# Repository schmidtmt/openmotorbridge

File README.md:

# OpenMotorBridge (v10.0) - Universal Motorcycle Intercom & Telemetry Bridge

<p align="center">
  
  &nbsp;&nbsp;&nbsp;&nbsp;&nbsp;&nbsp;&nbsp;&nbsp;
  
</p>

<p align="center">

</p>

**OpenMotorBridge (OMB)** is an open-source, cross-vendor communication and telemetry bridge for motorcycles. It seamlessly interconnects proprietary wireless intercom systems (**Sena Mesh 3.0** and **Cardo DMC Gen2**) with an open **2.4 GHz / 868 MHz OpenMotorMesh (OMM)**, high-precision **GNSS Tour Logging (Automotive Dead Reckoning)**, and a **wireless WebBLE PWA cockpit dashboard**.

---

## 📚 Technical Documentation

The comprehensive technical specification is split into 18 logically organized chapters:

1. [**01 - System Architecture & Satellite Topology**](docs/en/01_system_architecture.md)  
   *The 5 standardized functional nodes, de-sensing philosophy, RF diversity, whitepaper engineering decisions, and cockpit integration.*

2. [**02 - Intercom Matrix, Hardware Profiles & Routing**](docs/en/02_intercom_matrix_profiles.md)  
   *The 5 OEM adapter classes A-E, LittleFS profile engine, zero-latency PTT (< 1.8 ms), and audio cross-matrix.*

3. [**03 - Audio DSP, Acoustics & Knowles MEMS Wind Tracking**](docs/en/03_audio_dsp_acoustics.md)  
   *1500V Bourns isolation, ES8388 Codec, Knowles MEMS acoustic wind sampling, and Raised-Cosine Ducking.*

4. [**04 - Mesh Network, LoRa & GNSS Navigation**](docs/en/04_mesh_lora_navigation.md)  
   *OpenMotorMesh (OMM), Dynamic Leader Election (DLE), 868 MHz LoRa fallback, and 10 Hz Multi-GNSS.*

5. [**05 - Power Management, UPS Battery & Power Gate**](docs/en/05_power_management_ups.md)  
   *LM5164-Q1 72V buck, BQ24075 UPS, TPS25921 Quad-eFuse, Front Node TPS54302 / SW3526 30W PD & 1-click CarPlay hard reboot.*

6. [**06 - Telemetry Blackbox, SDIO Ringbuffer & WebDAV Sync**](docs/en/06_telemetry_blackbox_webdav.md)  
   *4-bit high-speed SDIO, GDPR/court-compliant ringbuffer, ECDSA SHA-256, and automated private cloud sync.*

7. [**07 - Hardware Architecture & Board Pinouts (All 10 PCBAs)**](docs/en/07_pcba_hardware_pinouts.md)  
   *All 10 active circuit boards: layer stackup, controlled impedance, net classes, functional zoning, and pinout tables (`PCBA 01`, `03`, `05`, `05B`, `05C`, `05D`, `07`, `08`, `09`, `10`).*

8. [**08 - Mechanical Enclosures, CAD & Reference Mounting Kits**](docs/en/08_enclosures_mechanics_cad.md)  
   *Screwless Dual-Rail Slide-In Monocoques (Type A & B), Under-Perch Mirror Pod (`PCBA 05C`), 5-Port Glovebox Hub (`PCBA 05B`), Sensor Puck (`PCBA 05D`), Radar 2.0 Winged Housing with Garmin Bayonet, and 4-pin IP67 magnetic breakaway couplers.*

9. [**09 - Firmware Architecture, FreeRTOS & Rollback-OTA**](docs/en/09_firmware_architecture.md)  
   *Multi-core ESP32-S31 (Main) & ESP32-P4 + ESP32-E22 (Front), Pod Co-Processors (ESP32-C6), ESP-NOW low-latency protocol (< 1.8 ms), and dual-bank rollback OTA.*

10. [**10 - WebApp PWA & Dashboard Operation**](docs/en/10_webapp_pwa_dashboard.md)  
    *Zero-cloud PWA web app, Web Bluetooth API (WebBLE), vehicle dynamics HUD, Front Node controls, Support-Van / Convoy profile modes, and 4-tier GPX export.*

11. [**11 - Smart-Managed CarPlay & Android Auto Bridge Architecture (PCBA 05)**](docs/en/11_carplay_android_auto_bridge_architecture.md)  
    *Harley Skyline OS / Boom! Box integration, CP2AA protocol bridge, Virtual WHIM bypass, source-gated handlebar controls & headless dongle management.*

12. [**12 - Vehicle CAN-Bus Profiles, DBC JSON Schema & Universal Telemetry Engine**](docs/en/12_can_bus_vehicle_profiles.md)  
    *Data-driven LittleFS profiles for Harley-Davidson, BMW Motorrad, KTM, and OBD2, passive listen-only protection, and EKF tunnel dead reckoning.*

13. [**13 - Digital Simulation & Multi-Physics Master Testbench**](docs/en/13_simulation_testbench.md)  
    *9 modular Python testbenches and 10 HIL scenarios verifying SPICE, thermal, transients, RF, and acoustics.*

14. [**14 - EMC Hardening, RF Shielding & Environmental Protection**](docs/en/14_emv_rf_hardening.md)  
    *Automotive transient immunity (ISO 7637-2), 2.4 GHz vs 868 MHz isolation, IPC-CC-830B coating, and shock damping.*

15. [**15 - Bill of Materials (BOM) & SMT Manufacturing (All 10 PCBAs)**](docs/en/15_bom_manufacturing.md)  
    *Complete 10-board BOM for JLCPCB SMT production, ordering checklist, two-cable backbone harness, and COTS items.*

16. [**16 - Build Instructions, Wiring & Vehicle Installation**](docs/en/16_build_instructions_assembly.md)  
    *Step-by-step assembly guide for screwless v10 Slide-In Monocoques, 3D printing parameters (FDM vs. MJF), Front Node & Glovebox Hub mounting, Harley 4-pin magnetic side-wall pass-through, Smart-Keyfob build, and commissioning.*

17. [**17 - Automotive Standards & Technical References**](docs/en/17_standards_references.md)  
    *Index for ISO 7637-2, ISO 16750, ECE R10, RED 2014/53/EU, IEC 61672-1 Class 1, and Bluetooth SIG.*

18. [**18 - Legal Compliance, Privacy (GDPR) & Licensing**](docs/en/18_legal_compliance_dsgvo.md)  
    *Open-source licenses (GPL-3.0, CERN-OHL-S v2, CC BY-SA 4.0), GDPR compliance, and liability disclaimer.*

---

## 🛠️ Repository Layout

* **`docs/de/`**: Complete technical specifications in German.
* **`docs/en/`**: Complete technical specifications in English.
* **`firmware/main_controller/`**: ESP-IDF / C++ source code for the central main box (ESP32-S31, PCBA 01).
* **`firmware/front_node/`**: ESP-IDF / C++ source code for the Universal Front Node (ESP32-P4 + ESP32-E22, PCBA 05).
* **`firmware/smart_cartridge/`**: ESP-IDF / C++ source code for Saddlebag Pod Gateways Pod 1 & 2 (ESP32-C6, PCBA 03).
* **`firmware/radar_submcu/`**: ESP-IDF / C++ source code for Heck-Radar 2.0 Sub-MCU & Halo Wings (ESP32-C5, PCBA 08).
* **`webapp_pwa/`**: Zero-cloud offline WebBLE dashboard (HTML5, Vanilla JS, CSS3, Service Worker, i18n).
* **`hardware/`**: KiCad schematics, Gerber files, and 3D enclosure CAD models.
* **`tools/audio_testbench/`**: **Interactive Live Audio DSP Studio & Real-Time Testbench** (`python3 tools/audio_testbench/server.py` $\rightarrow$ Web Audio testbench with live mic, Spacebar PTT, speedometer & ducking).
* **`tools/simulators/`**: 9 modular Python simulation testbenches (`python3 tools/run_all_simulations.py`).

---

## 📜 Licenses

* **Hardware & PCB Layouts:** [CERN-OHL-S v2](https://ohwr.org/project/cernohl/wikis/Documents/CERN-OHL-version-2) (Strongly Reciprocal)
* **Firmware & Web Dashboard:** [GNU General Public License v3.0 (GPL-3.0)](https://www.gnu.org/licenses/gpl-3.0.html)
* **Documentation & 3D Models:** [Creative Commons Attribution-ShareAlike 4.0 International (CC BY-SA 4.0)](https://creativecommons.org/licenses/by-sa/4.0/)

---

## ⚠️ Liability Disclaimer

All information, schematics, board layouts, 3D printing files, and software published in this project are provided free of charge on an "AS IS" basis. Assembly, installation, and operation occur entirely at the user's own risk. All mentioned brand names (Harley-Davidson®, BMW®, Garmin®, Sena®, Cardo®, Apple CarPlay®) are registered trademarks of their respective owners.

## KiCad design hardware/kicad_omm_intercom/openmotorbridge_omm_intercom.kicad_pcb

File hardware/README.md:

# OpenMotorBridge v8.5 / v9.0 - KiCad Hardware-Baukasten (Clean All-UWB Architecture)

Dieses Verzeichnis enthält die vollständigen **KiCad 10 Schaltplan-, PCB- und Produktionsdateien** für die drahtlose **All-UWB & Pure-DC Architektur** von OpenMotorBridge.

---

## 📂 Das bereinigte 6-Platinen-Lineup

Durch den konsequenten Einsatz von Ultra-Wideband (Qorvo DW3110 6.5 GHz Ch. 5, $< 0{,}4\,\text{ms}$) und Bluetooth entfällt jegliche Signal- und NF-Audioverdrahtung über den Rahmen. Der Kabelbaum besteht ausschließlich aus robusten **2-Draht-DC-Power-Peitschen** (+5V/GND bzw. +12V/GND). 

Die Pod-Platine (`PCBA 02`) und der Heck-Pod (`PCBA 04`) sind ersatzlos entfallen - der Baukasten besteht aus **exakt 6 aktiven PCBAs**:

| PCBA | Baugruppe & Funktion | Maße / Lagen | Kern-Komponenten / RF |
| :--- | :--- | :--- | :--- |
| **PCBA 01** | **Zentralbox Main Controller**<br>*(Unter Sitzbank, Audio-DSP, USV)* | 85 x 55 mm<br>4 Lagen (ENIG) | ESP32-S3, ES8388 24-Bit Codec, TCAN334G CAN-FD, LM5164-Q1, SX1262 LoRa (Top), DW3110 UWB (Bottom), SW1 Taster |
| **PCBA 03** | **Universal Smart Cartridge Rev 3.0**<br>*(Autarker UWB-Funkschlitten)* | 35 x 25 mm<br>2 Lagen (ENIG, 2-seitig SMT) | Qorvo DW3110 UWB, SPI Host-MCU, 4x AO3400A MOSFETs, 2P Frontkontakt (+5V/GND), DNP-Codec |
| **PCBA 05** | **Universal Front-Knoten**<br>*(Cockpit Hub, Sensorik, Audio, USB-PD)* | 82 x 50 mm<br>4 Lagen (ENIG) | ESP32-S3, DW3110 UWB, SAM-M10Q, USB2514B Hub, Dual SW3526 PD20W, Qi 12V, BSD LEDs |
| **PCBA 06** | **MagSafe Frame Dock Adapter**<br>*(Rahmendock M8 auf 2-Pin MagSafe)* | 28 x 11.5 mm<br>2 Lagen (1 oz) | 2 Pogo-Pins (+5V / GND), TVS Diode, 16V PPTC Polyfuse |
| **PCBA 07** | **2-in-1 LoRa Smart-Keyfob & Pager**<br>*(Taschen-Pager, N52 Key & Qi)* | 38 x 19 mm<br>2 Lagen (ENIG) | Nordic nRF52840 SoC, Semtech SX1262 LoRa, DRV2605L Haptik, BQ51003 Qi RX |
| **PCBA 08** | **Radar 2.0 Sub-MCU & Wings**<br>*(Wheeltec 77GHz MR20 + Halo LED)* | 115 x 65 mm<br>2 Lagen (ENIG) | ESP32 Sub-MCU (UWB DW3110), 36x WS2812B LEDs, 2-Pin 12V Power |

---

## 🔌 Zentraler Bordnetz-Stecker (Deutsch DTM-12 Automotive)

Die Zentralbox nutzt einen robusten, wasserdichten **Deutsch DTM-12 Industriestecker** (11 aktive Kontakte):

| Pin | Signalname | Funktion | Querschnitt / Ziel |
| :---: | :--- | :--- | :--- |
| **1** | `KL30_IN` | 12V Dauerplus | AWG20 (0.50 mm²) / Bordnetz |
| **2** | `KL15_IGN` | 12V Zündungsplus | AWG22 (0.34 mm²) / Zündung |
| **3** | `VEHICLE_GND`| Hauptmasse (KL31) | AWG20 (0.50 mm²) / Rahmen |
| **4** | `CAN_H` | Fahrzeug-CAN High | AWG24 (0.22 mm²) / Twisted Pair |
| **5** | `CAN_L` | Fahrzeug-CAN Low | AWG24 (0.22 mm²) / Twisted Pair |
| **6** | `POD1_VCC` | 5V Switched Power Bucht 1 (Links) | AWG22 (0.34 mm²) / JWPF 2P |
| **7** | `POD1_GND` | Masse Bucht 1 (Links) | AWG22 (0.34 mm²) / JWPF 2P |
| **8** | `POD2_VCC` | 5V Switched Power Bucht 2 (Rechts) | AWG22 (0.34 mm²) / JWPF 2P |
| **9** | `POD2_GND` | Masse Bucht 2 (Rechts) | AWG22 (0.34 mm²) / JWPF 2P |
| **10**| `RADAR_PWR` | 12V Switched Power Radar Heck | AWG22 (0.34 mm²) / JWPF 2P |
| **11**| `RADAR_GND` | Masse Radar | AWG22 (0.34 mm²) / JWPF 2P |
| **12**| `CHASSIS_EARTH` | Gehäuseschirm / Rahmenerde | AWG20 (0.50 mm²) |

---

## 🛠️ Fertigung & Validierung (JLCPCB / Eurocircuits)

* **Produktionspakete generieren:**
  ```bash
  python3 hardware/scripts/export_manufacturing_packages.py
  ```
* **JLCPCB DFM & Netlist-Verifikation:**
  ```bash
  /Applications/KiCad/KiCad.app/Contents/Frameworks/Python.framework/Versions/3.9/bin/python3 hardware/scripts/verify_pcb_designs_jlcpcb.py
  ```

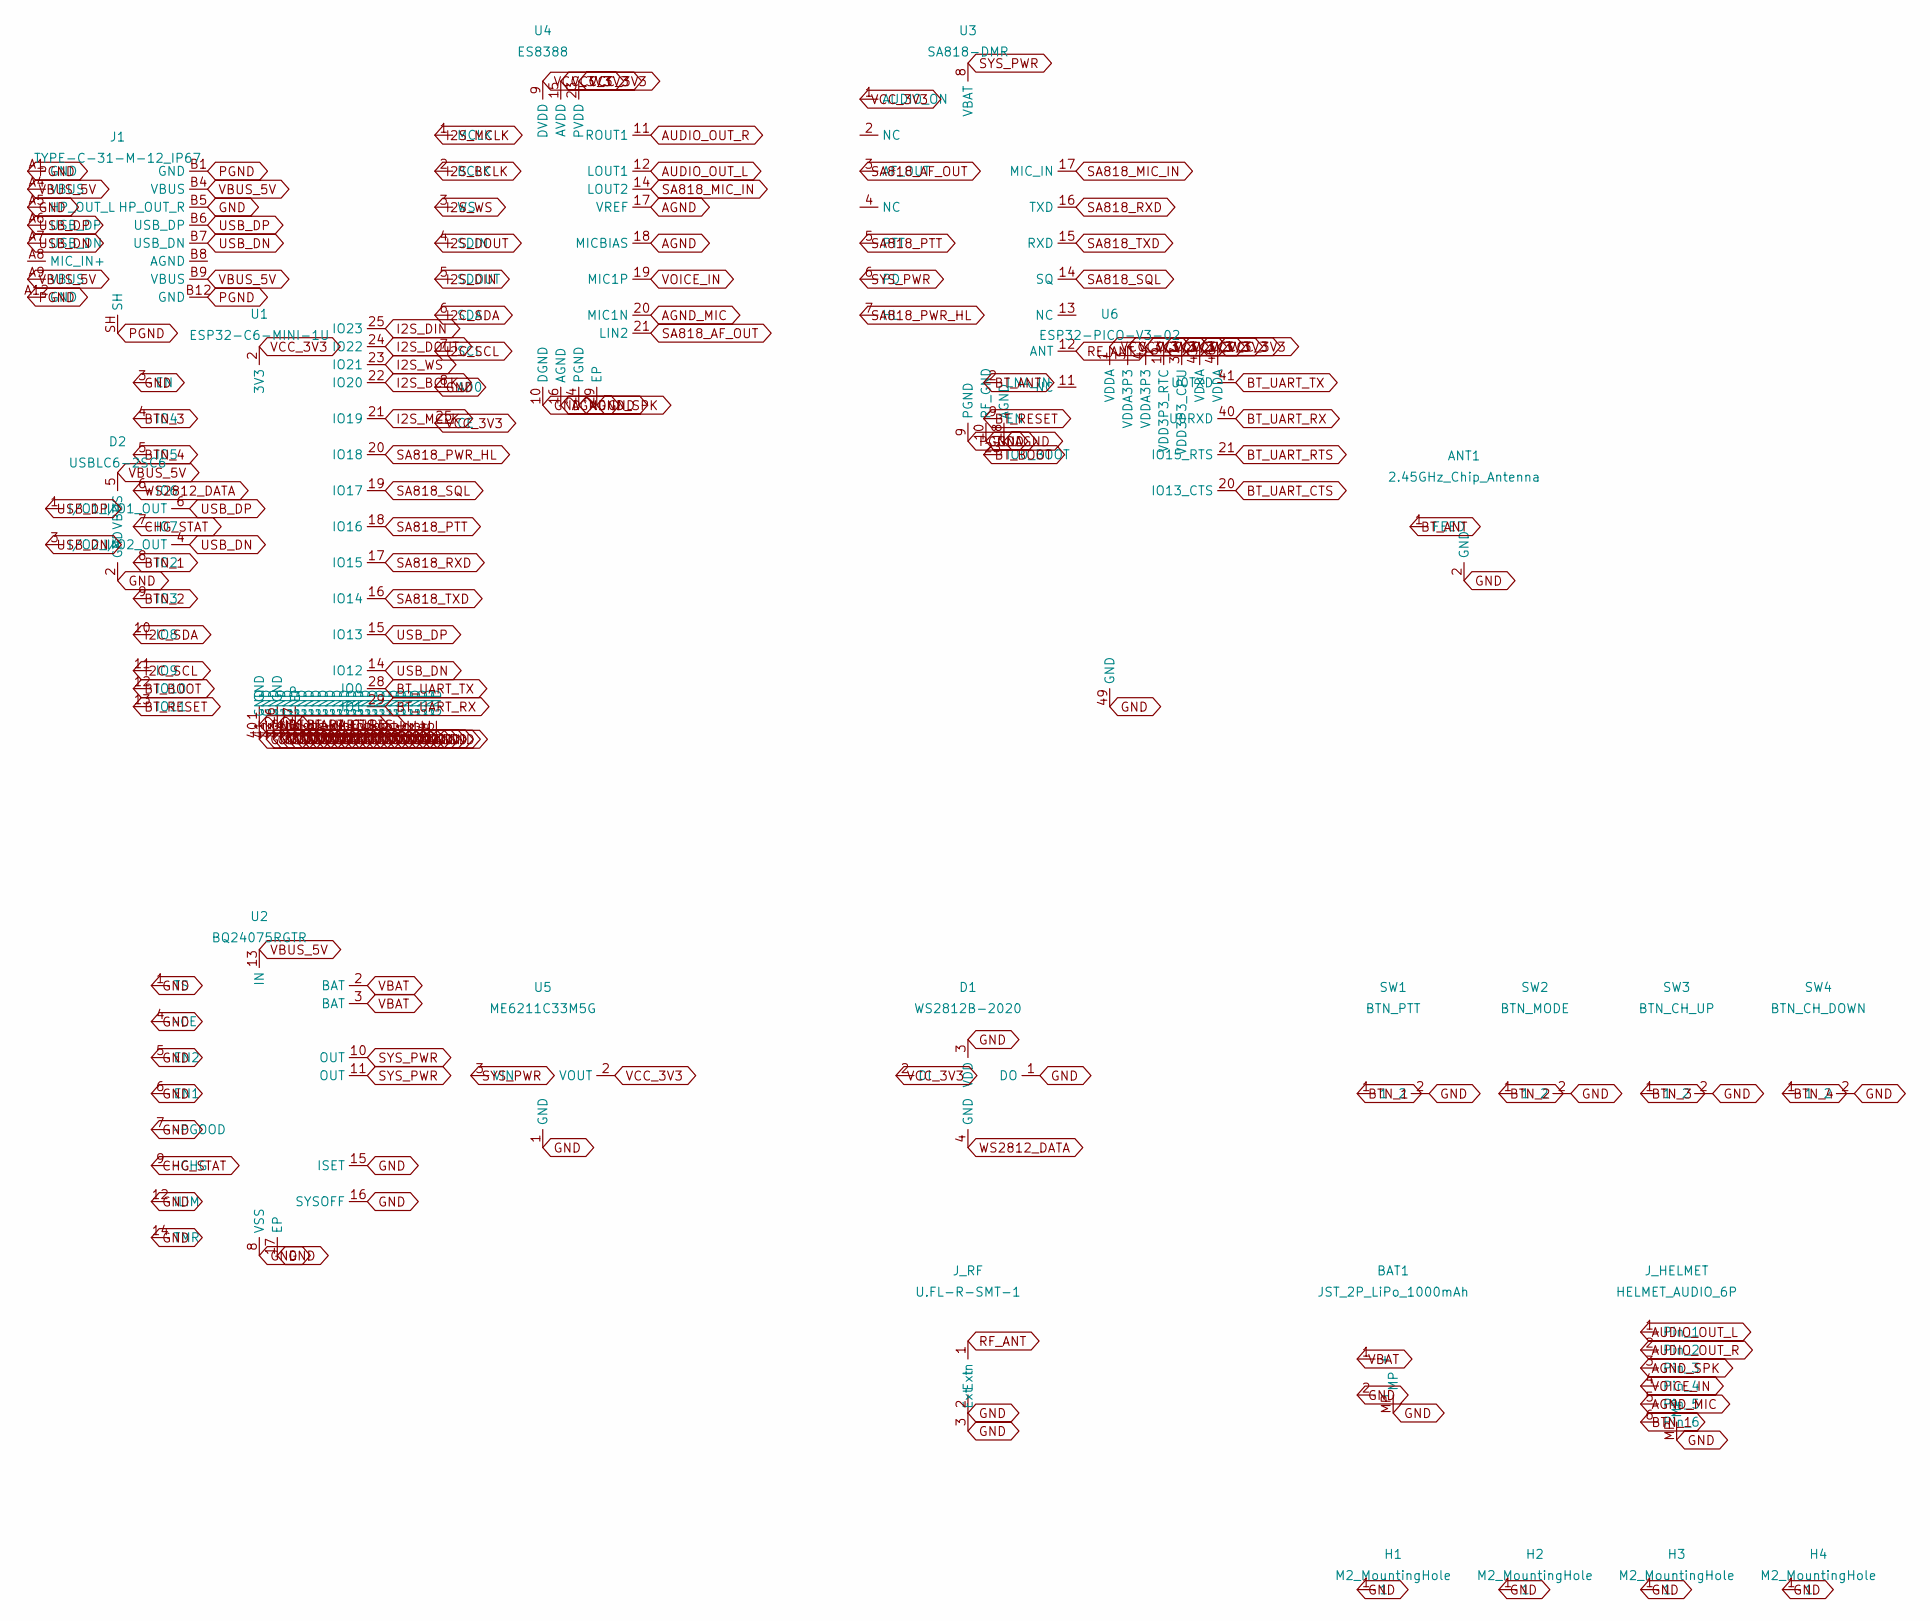
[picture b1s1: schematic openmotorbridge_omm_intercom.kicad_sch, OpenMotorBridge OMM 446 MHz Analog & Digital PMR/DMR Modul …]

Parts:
ANT1: 2.45GHz_Chip_Antenna; Johanson_2450AT18x100; LCSC C2909988
BAT1: JST_2P_LiPo_1000mAh; JST_SH_BM02B-SRSS-TB_1x02-1MP_P1.00mm_Vertical
D1: WS2812B-2020; LED_WS2812B-2020_PLCC4_2.0x2.0mm
D2: USBLC6-2SC6; SOT-23-6
H1, H2, H3, H4: M2_MountingHole; MountingHole_2.2mm_M2_Pad
J1: TYPE-C-31-M-12_IP67; USB_C_Receptacle_HRO_TYPE-C-31-M-12
J_HELMET: HELMET_AUDIO_6P; JST_SH_BM06B-SRSS-TB_1x06-1MP_P1.00mm_Vertical
J_RF: U.FL-R-SMT-1; U.FL_Hirose_U.FL-R-SMT-1_Vertical
SW1: BTN_PTT; SW_Push_SPST_NO_Alps_SKRK
SW2: BTN_MODE; SW_Push_SPST_NO_Alps_SKRK
SW3: BTN_CH_UP; SW_Push_SPST_NO_Alps_SKRK
SW4: BTN_CH_DOWN; SW_Push_SPST_NO_Alps_SKRK
U1: ESP32-C6-MINI-1U; ESP32-S2-MINI-1U
U2: BQ24075RGTR; VQFN-16-1EP_3x3mm_P0.5mm_EP1.8x1.8mm
U3: SA818-DMR; NiceRF_SA818-DMR_SMD_38x16mm
U4: ES8388; QFN-28-1EP_4x4mm_P0.4mm_EP2.4x2.4mm
U5: ME6211C33M5G; SOT-23
U6: ESP32-PICO-V3-02; QFN-48-1EP_7x7mm_P0.5mm_EP5.3x5.3mm; LCSC C2686884

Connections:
AGND: U3.18 (AGND), U4.16 (AGND), U4.17 (VREF), U4.18 (MICBIAS)
AGND_MIC: J_HELMET.5, U4.20 (MIC1N)
AGND_SPK: J_HELMET.3, U4.24 (PGND)
AUDIO_OUT_L: J_HELMET.1, U4.12 (LOUT1)
AUDIO_OUT_R: J_HELMET.2, U4.11 (ROUT1)
BTN_1: J_HELMET.6, SW1.1, U1.8 (IO2)
BTN_2: SW2.1, U1.9 (IO3)
BTN_3: SW3.1, U1.4 (IO4)
BTN_4: SW4.1, U1.5 (IO5)
BT_ANT: ANT1.1 (FEED), U6.2 (LNA_IN)
BT_BOOT: U1.12 (IO10), U6.23 (IO0_BOOT)
BT_RESET: U1.13 (IO11), U6.9 (EN)
BT_UART_CTS: U1.26 (GND), U6.20 (IO13_CTS)
BT_UART_RTS: U1.27 (EP), U6.21 (IO15_RTS)
BT_UART_RX: U1.29 (IO1), U6.40 (U0RXD)
BT_UART_TX: U1.28 (IO0), U6.41 (U0TXD)
CHG_STAT: U1.7 (IO7), U2.9 (~CHG)
GND: ANT1.2 (GND), BAT1.2 (-), BAT1.MP, D1.1 (DO), D1.3 (VDD), D2.2 (GND), H1.1, H2.1, H3.1, H4.1, J1.A5 (HP_OUT_L), J1.B5 (HP_OUT_R), J_HELMET.MP, J_RF.2 (Ext), J_RF.3 (Ext), SW1.2, SW2.2, SW3.2, SW4.2, U1.1 (GND), U1.3 (EN), U1.40 (GND), U1.41 (GND), U1.42 (GND), U1.43 (GND), U1.44 (GND), U1.45 (GND), U1.46 (GND), U1.47 (GND), U1.48 (GND), U1.49 (GND), U1.50 (GND), U1.51 (GND), U1.52 (GND), U1.53 (GND), U1.54 (GND), U1.55 (GND), U1.56 (GND), U1.57 (GND), U1.58 (GND), U1.59 (GND), U1.60 (GND), U1.61 (GND), U1.62 (GND), U1.63 (GND), U1.64 (GND), U1.65 (GND), U2.1 (TS), U2.4 (~CE), U2.5 (EN2), U2.6 (EN1), U2.7 (~PGOOD), U2.8 (VSS), U2.12 (ILIM), U2.14 (TMR), U2.15 (ISET), U2.16 (SYSOFF), U2.17 (EP), U3.10 (RF_GND), U4.8 (AD0), U4.10 (DGND), U4.29 (EP), U5.1 (GND), U6.49 (GND)
I2C_SCL: U1.11 (IO9), U4.7 (SCL)
I2C_SDA: U1.10 (IO8), U4.6 (SDA)
I2S_BCLK: U1.22 (IO20), U4.2 (BCLK)
I2S_DIN: U1.25 (IO23), U4.5 (SDOUT)
I2S_DOUT: U1.24 (IO22), U4.4 (SDIN)
I2S_MCLK: U1.21 (IO19), U4.1 (MCLK)
I2S_WS: U1.23 (IO21), U4.3 (WS)
PGND: J1.A1 (GND), J1.A12 (GND), J1.B1 (GND), J1.B12 (GND), J1.SH, U3.9 (PGND)
RF_ANT: J_RF.1 (In), U3.12 (ANT)
SA818_AF_OUT: U3.3 (AF_OUT), U4.21 (LIN2)
SA818_MIC_IN: U3.17 (MIC_IN), U4.14 (LOUT2)
SA818_PTT: U1.18 (IO16), U3.5 (PTT)
SA818_PWR_HL: U1.20 (IO18), U3.7 (HL)
SA818_RXD: U1.17 (IO15), U3.16 (TXD)
SA818_SQL: U1.19 (IO17), U3.14 (SQ)
SA818_TXD: U1.16 (IO14), U3.15 (RXD)
SYS_PWR: U2.10 (OUT), U2.11 (OUT), U3.6 (PD), U3.8 (VBAT), U5.3 (VIN)
USB_DN: D2.3 (I/O2_IN), D2.4 (I/O2_OUT), J1.A7 (USB_DN), J1.B7 (USB_DN), U1.14 (IO12)
USB_DP: D2.1 (I/O1_IN), D2.6 (I/O1_OUT), J1.A6 (USB_DP), J1.B6 (USB_DP), U1.15 (IO13)
VBAT: BAT1.1 (+), U2.2 (BAT), U2.3 (BAT)
VBUS_5V: D2.5 (VBUS), J1.A4 (VBUS), J1.A9 (VBUS), J1.B4 (VBUS), J1.B9 (VBUS), U2.13 (IN)
VCC_3V3: D1.2 (DI), U1.2 (3V3), U3.1 (AUDIO_ON), U4.9 (DVDD), U4.15 (AVDD), U4.23 (PVDD), U4.25 (CE), U5.2 (VOUT), U6.1 (VDDA), U6.3 (VDDA3P3), U6.4 (VDDA3P3), U6.19 (VDD3P3_RTC), U6.37 (VDD3P3_CPU), U6.43 (VDDA), U6.46 (VDDA)
VOICE_IN: J_HELMET.4, U4.19 (MIC1P)
WS2812_DATA: D1.4 (GND), U1.6 (IO6)

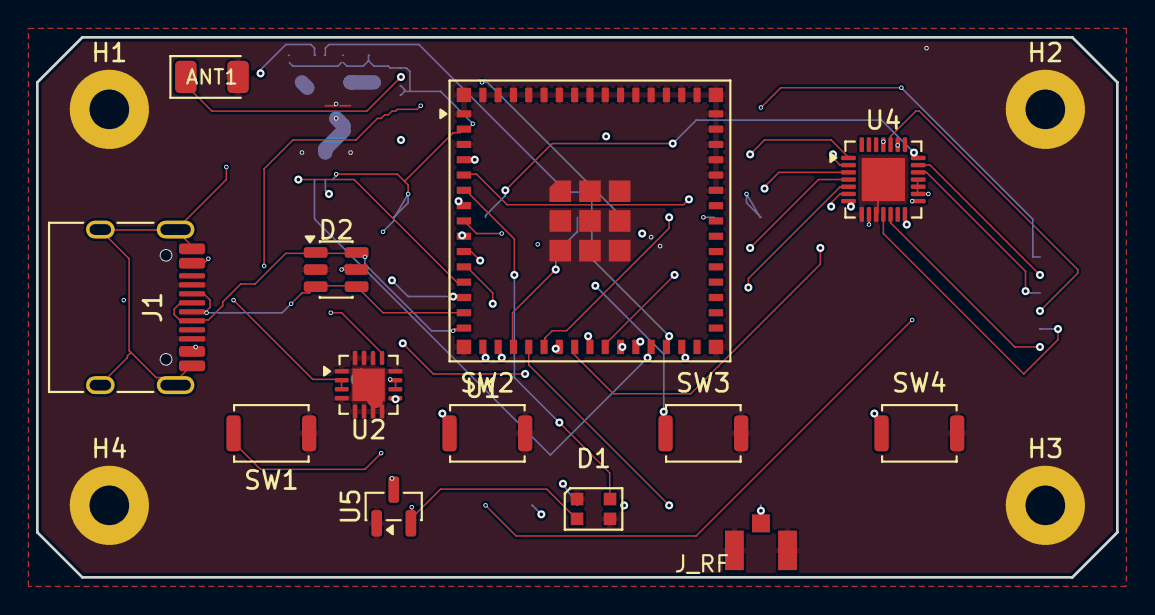
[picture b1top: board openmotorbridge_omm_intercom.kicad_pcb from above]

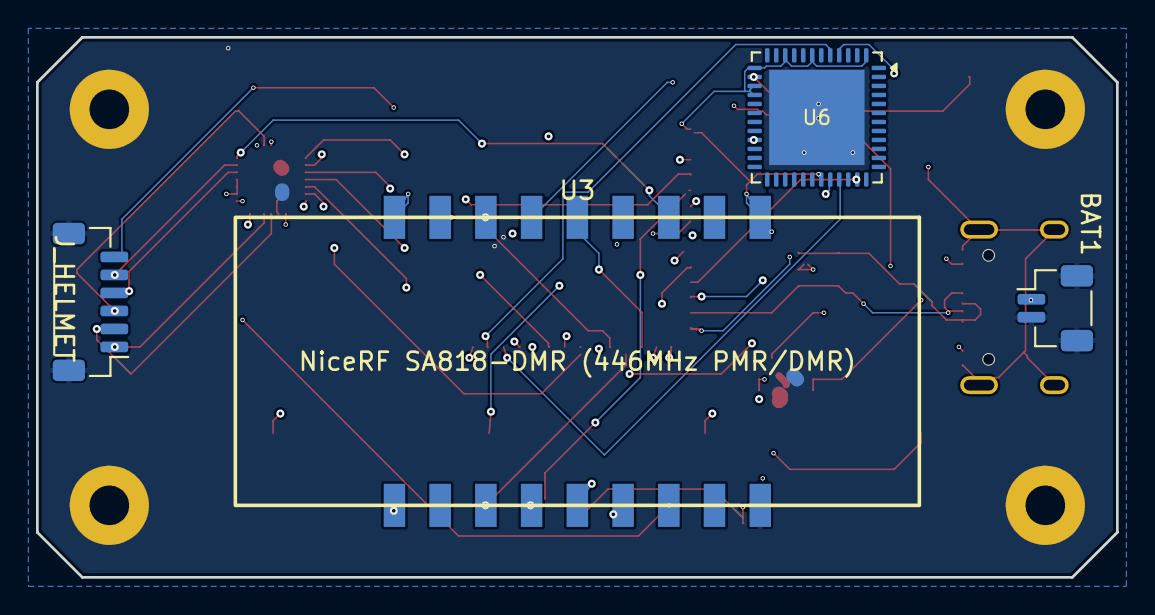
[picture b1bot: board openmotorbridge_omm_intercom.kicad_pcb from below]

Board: 4 copper layers, 60.0 x 30.0 mm, 21 parts (4 on the bottom side), 42 nets.

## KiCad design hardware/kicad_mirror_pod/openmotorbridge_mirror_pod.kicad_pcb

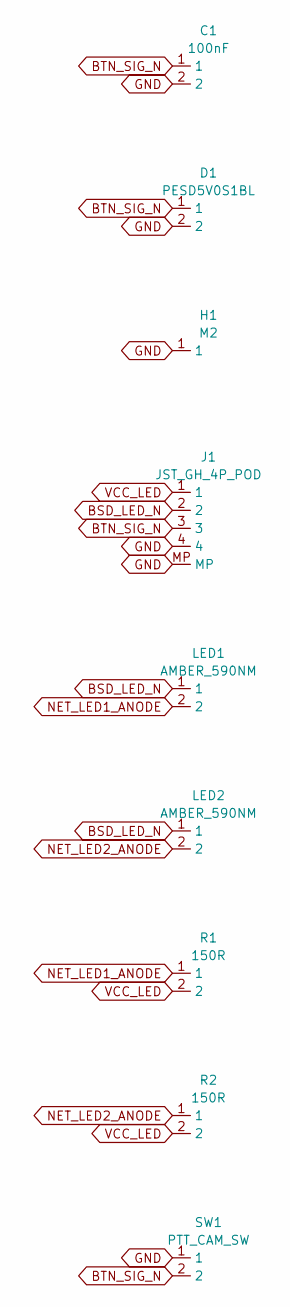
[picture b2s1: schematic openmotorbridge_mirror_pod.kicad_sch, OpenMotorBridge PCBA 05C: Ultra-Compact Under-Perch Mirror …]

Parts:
C1: 100nF; C_0603_1608Metric
D1: PESD5V0S1BL; D_SOD-323
H1: M2; MountingHole_2.2mm_M2_Pad
J1: JST_GH_4P_POD; JST_GH_SM04B-GHS-TB_1x04-1MP_P1.25mm_Horizontal
LED1, LED2: AMBER_590NM; LED_1206_3216Metric
R1, R2: 150R; R_0603_1608Metric
SW1: PTT_CAM_SW; SW_SPST_B3SL-1002P

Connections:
BSD_LED_N: J1.2, LED1.1, LED2.1
BTN_SIG_N: C1.1, D1.1, J1.3, SW1.2
GND: C1.2, D1.2, H1.1, J1.4, J1.MP, SW1.1
NET_LED1_ANODE: LED1.2, R1.1
NET_LED2_ANODE: LED2.2, R2.1
VCC_LED: J1.1, R1.2, R2.2

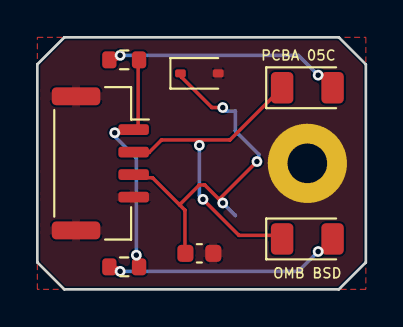
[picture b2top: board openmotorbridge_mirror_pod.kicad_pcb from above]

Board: 2 copper layers, 18.2 x 14.0 mm, 9 parts (1 on the bottom side), 6 nets.

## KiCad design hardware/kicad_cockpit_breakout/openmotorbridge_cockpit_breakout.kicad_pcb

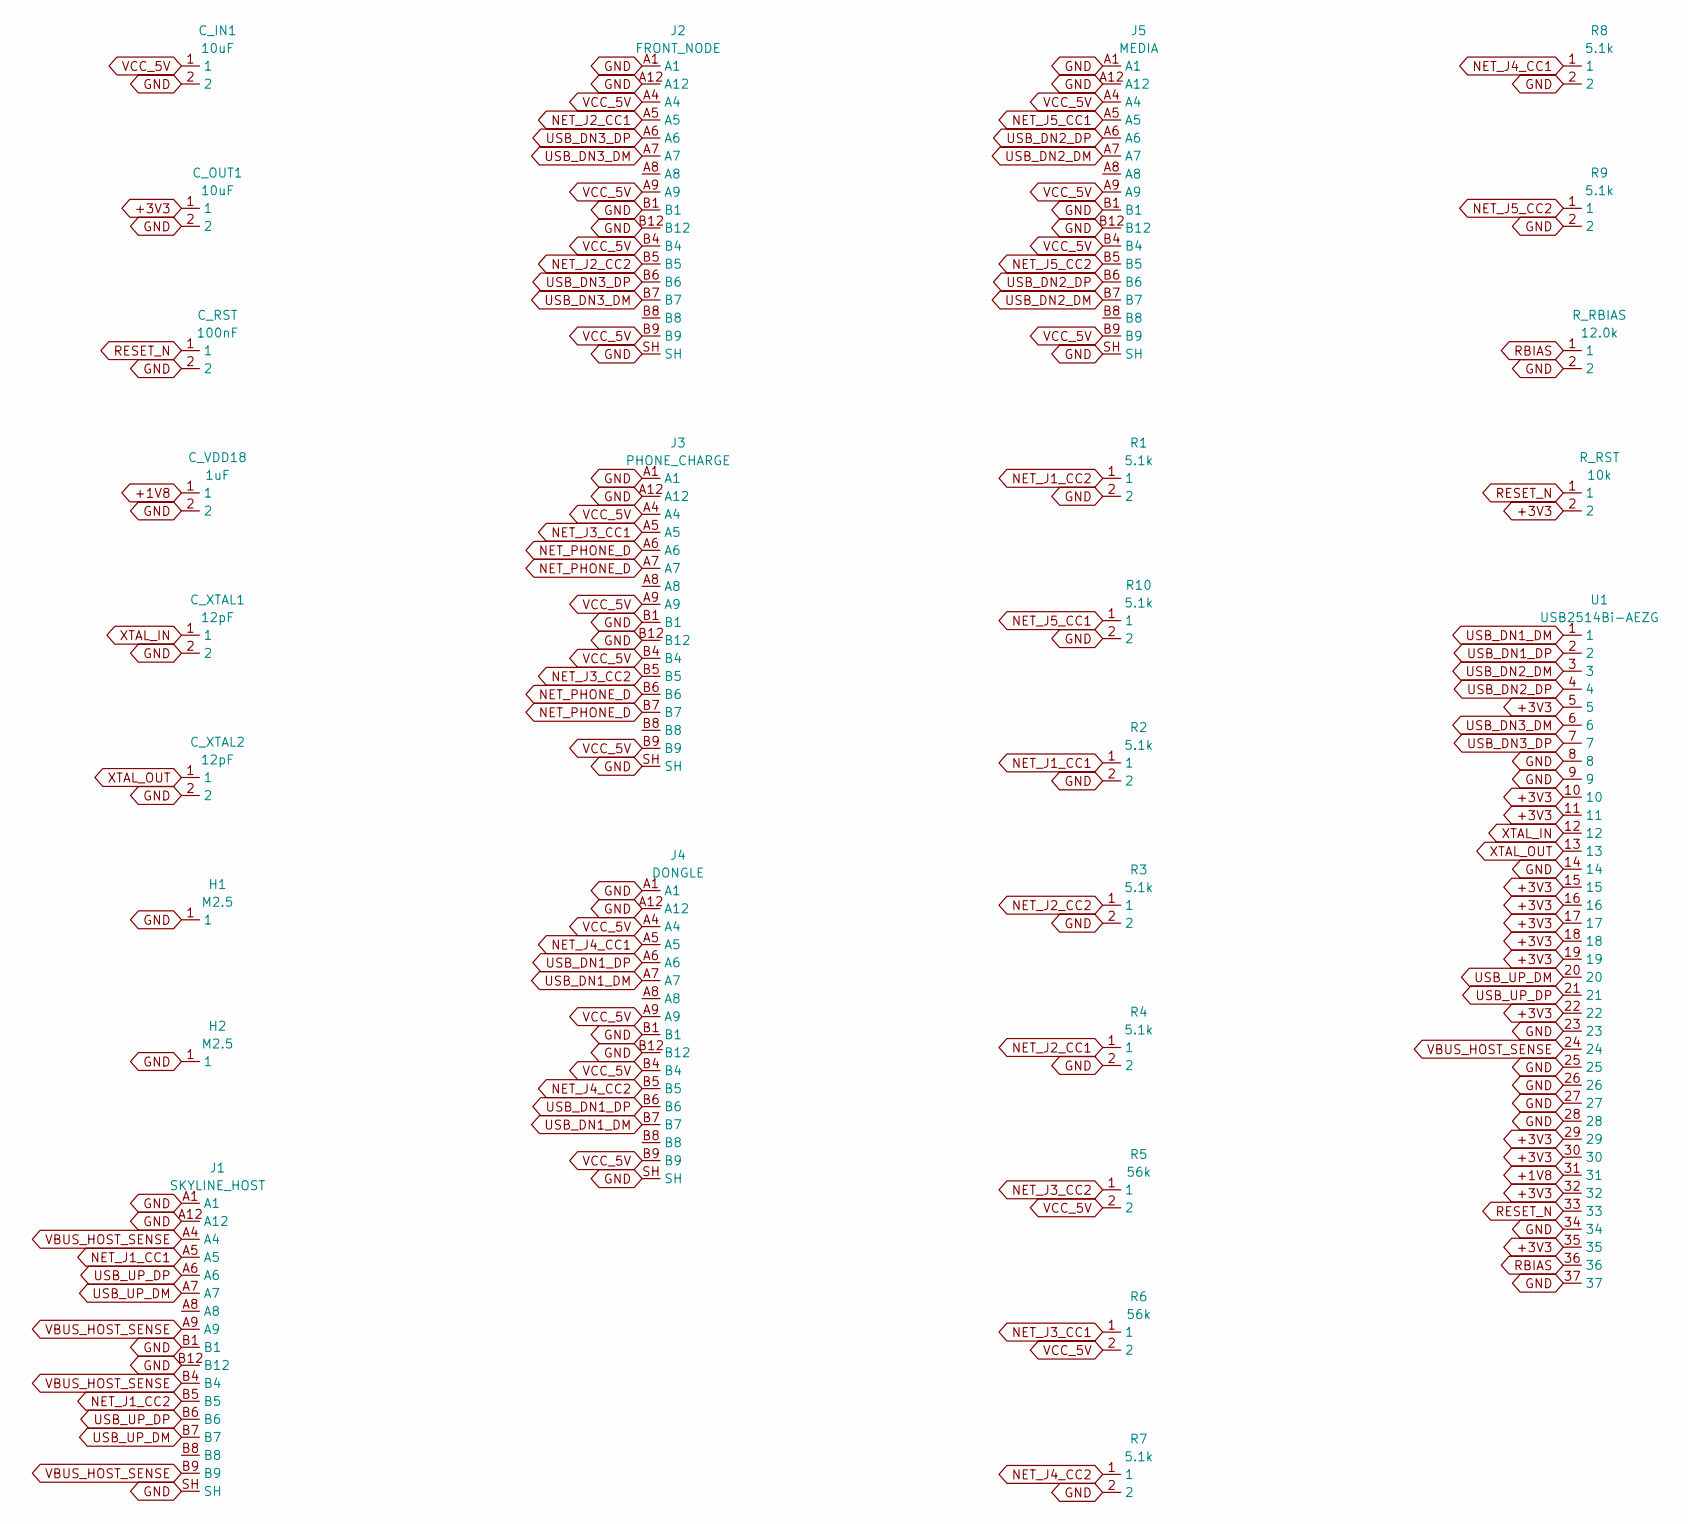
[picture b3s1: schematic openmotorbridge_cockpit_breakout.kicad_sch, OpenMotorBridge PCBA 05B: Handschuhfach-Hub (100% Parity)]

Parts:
C_IN1: 10uF; C_0603_1608Metric
C_OUT1: 10uF; C_0603_1608Metric
C_RST: 100nF; C_0603_1608Metric
C_VDD18: 1uF; C_0603_1608Metric
C_XTAL1, C_XTAL2: 12pF; C_0603_1608Metric
H1, H2: M2.5; MountingHole_2.7mm_M2.5_Pad
J1: SKYLINE_HOST; USB_C_Receptacle_HRO_TYPE-C-31-M-12
J2: FRONT_NODE; USB_C_Receptacle_HRO_TYPE-C-31-M-12
J3: PHONE_CHARGE; USB_C_Receptacle_HRO_TYPE-C-31-M-12
J4: DONGLE; USB_C_Receptacle_HRO_TYPE-C-31-M-12
J5: MEDIA; USB_C_Receptacle_HRO_TYPE-C-31-M-12
R1, R2, R3, R4, R7, R8, R9, R10: 5.1k; R_0603_1608Metric
R5, R6: 56k; R_0603_1608Metric
R_RBIAS: 12.0k; R_0603_1608Metric
R_RST: 10k; R_0603_1608Metric
U1: USB2514Bi-AEZG; QFN-36-1EP_6x6mm_P0.5mm_EP4.1x4.1mm

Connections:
+1V8: C_VDD18.1, U1.31
+3V3: C_OUT1.1, R_RST.2, U1.5, U1.10, U1.11, U1.15, U1.16, U1.17, U1.18, U1.19, U1.22, U1.29, U1.30, U1.32, U1.35
GND: C_IN1.2, C_OUT1.2, C_RST.2, C_VDD18.2, C_XTAL1.2, C_XTAL2.2, H1.1, H2.1, J1.A1, J1.A12, J1.B1, J1.B12, J1.SH, J2.A1, J2.A12, J2.B1, J2.B12, J2.SH, J3.A1, J3.A12, J3.B1, J3.B12, J3.SH, J4.A1, J4.A12, J4.B1, J4.B12, J4.SH, J5.A1, J5.A12, J5.B1, J5.B12, J5.SH, R1.2, R2.2, R3.2, R4.2, R7.2, R8.2, R9.2, R10.2, R_RBIAS.2, U1.8, U1.9, U1.14, U1.23, U1.25, U1.26, U1.27, U1.28, U1.34, U1.37
NET_J1_CC1: J1.A5, R2.1
NET_J1_CC2: J1.B5, R1.1
NET_J2_CC1: J2.A5, R4.1
NET_J2_CC2: J2.B5, R3.1
NET_J3_CC1: J3.A5, R6.1
NET_J3_CC2: J3.B5, R5.1
NET_J4_CC1: J4.A5, R8.1
NET_J4_CC2: J4.B5, R7.1
NET_J5_CC1: J5.A5, R10.1
NET_J5_CC2: J5.B5, R9.1
NET_PHONE_D: J3.A6, J3.A7, J3.B6, J3.B7
RBIAS: R_RBIAS.1, U1.36
RESET_N: C_RST.1, R_RST.1, U1.33
USB_DN1_DM: J4.A7, J4.B7, U1.1
USB_DN1_DP: J4.A6, J4.B6, U1.2
USB_DN2_DM: J5.A7, J5.B7, U1.3
USB_DN2_DP: J5.A6, J5.B6, U1.4
USB_DN3_DM: J2.A7, J2.B7, U1.6
USB_DN3_DP: J2.A6, J2.B6, U1.7
USB_UP_DM: J1.A7, J1.B7, U1.20
USB_UP_DP: J1.A6, J1.B6, U1.21
VBUS_HOST_SENSE: J1.A4, J1.A9, J1.B4, J1.B9, U1.24
VCC_5V: C_IN1.1, J2.A4, J2.A9, J2.B4, J2.B9, J3.A4, J3.A9, J3.B4, J3.B9, J4.A4, J4.A9, J4.B4, J4.B9, J5.A4, J5.A9, J5.B4, J5.B9, R5.2, R6.2
XTAL_IN: C_XTAL1.1, U1.12
XTAL_OUT: C_XTAL2.1, U1.13

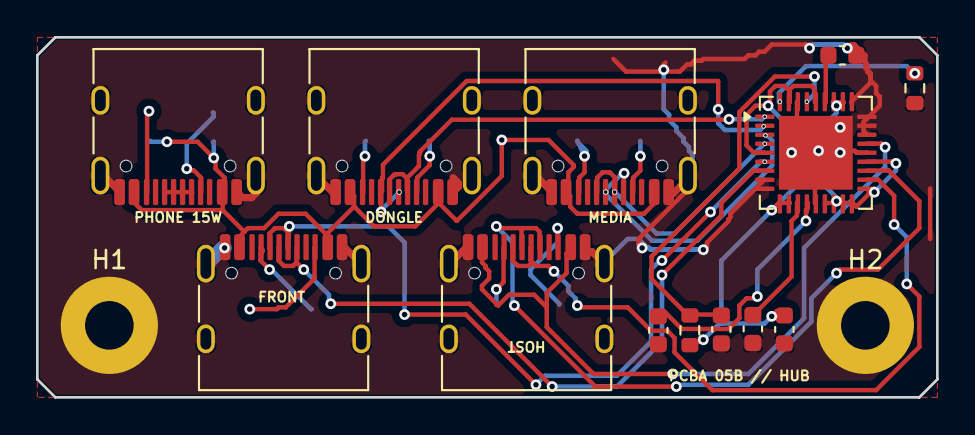
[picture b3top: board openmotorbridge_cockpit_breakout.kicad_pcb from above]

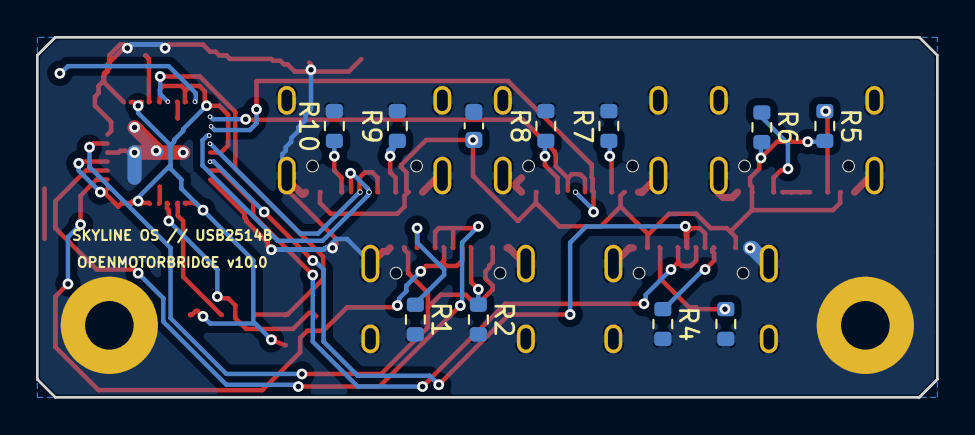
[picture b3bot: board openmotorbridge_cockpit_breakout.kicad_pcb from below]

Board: 2 copper layers, 50.0 x 20.0 mm, 26 parts (11 on the bottom side), 28 nets.

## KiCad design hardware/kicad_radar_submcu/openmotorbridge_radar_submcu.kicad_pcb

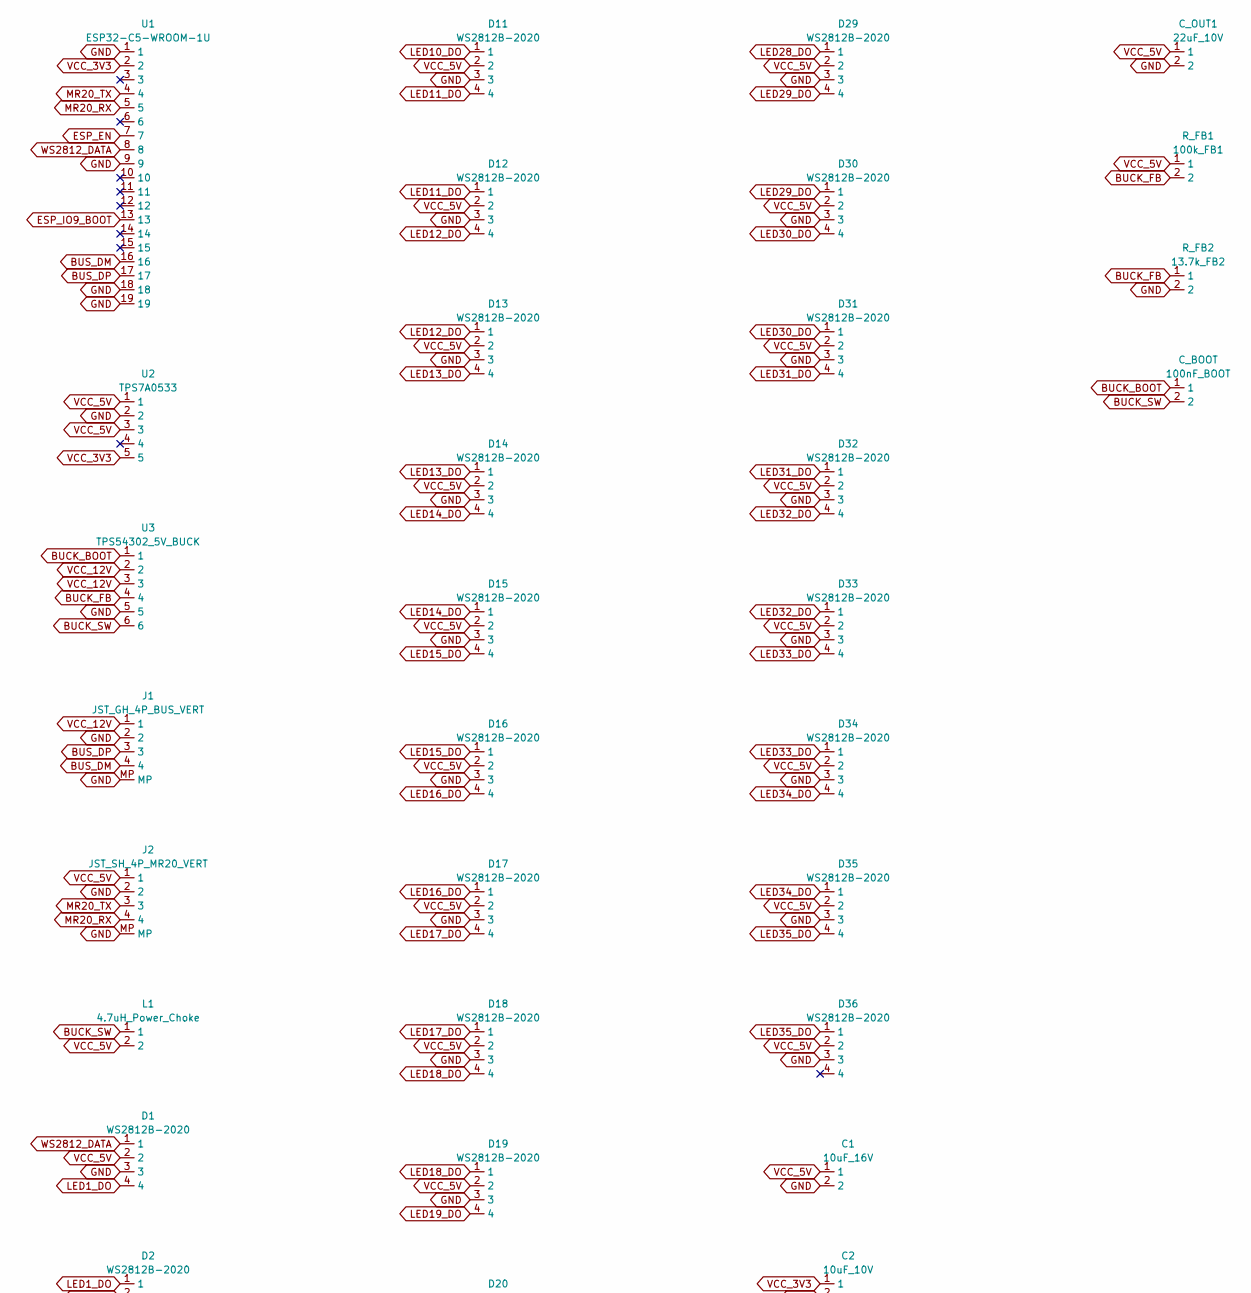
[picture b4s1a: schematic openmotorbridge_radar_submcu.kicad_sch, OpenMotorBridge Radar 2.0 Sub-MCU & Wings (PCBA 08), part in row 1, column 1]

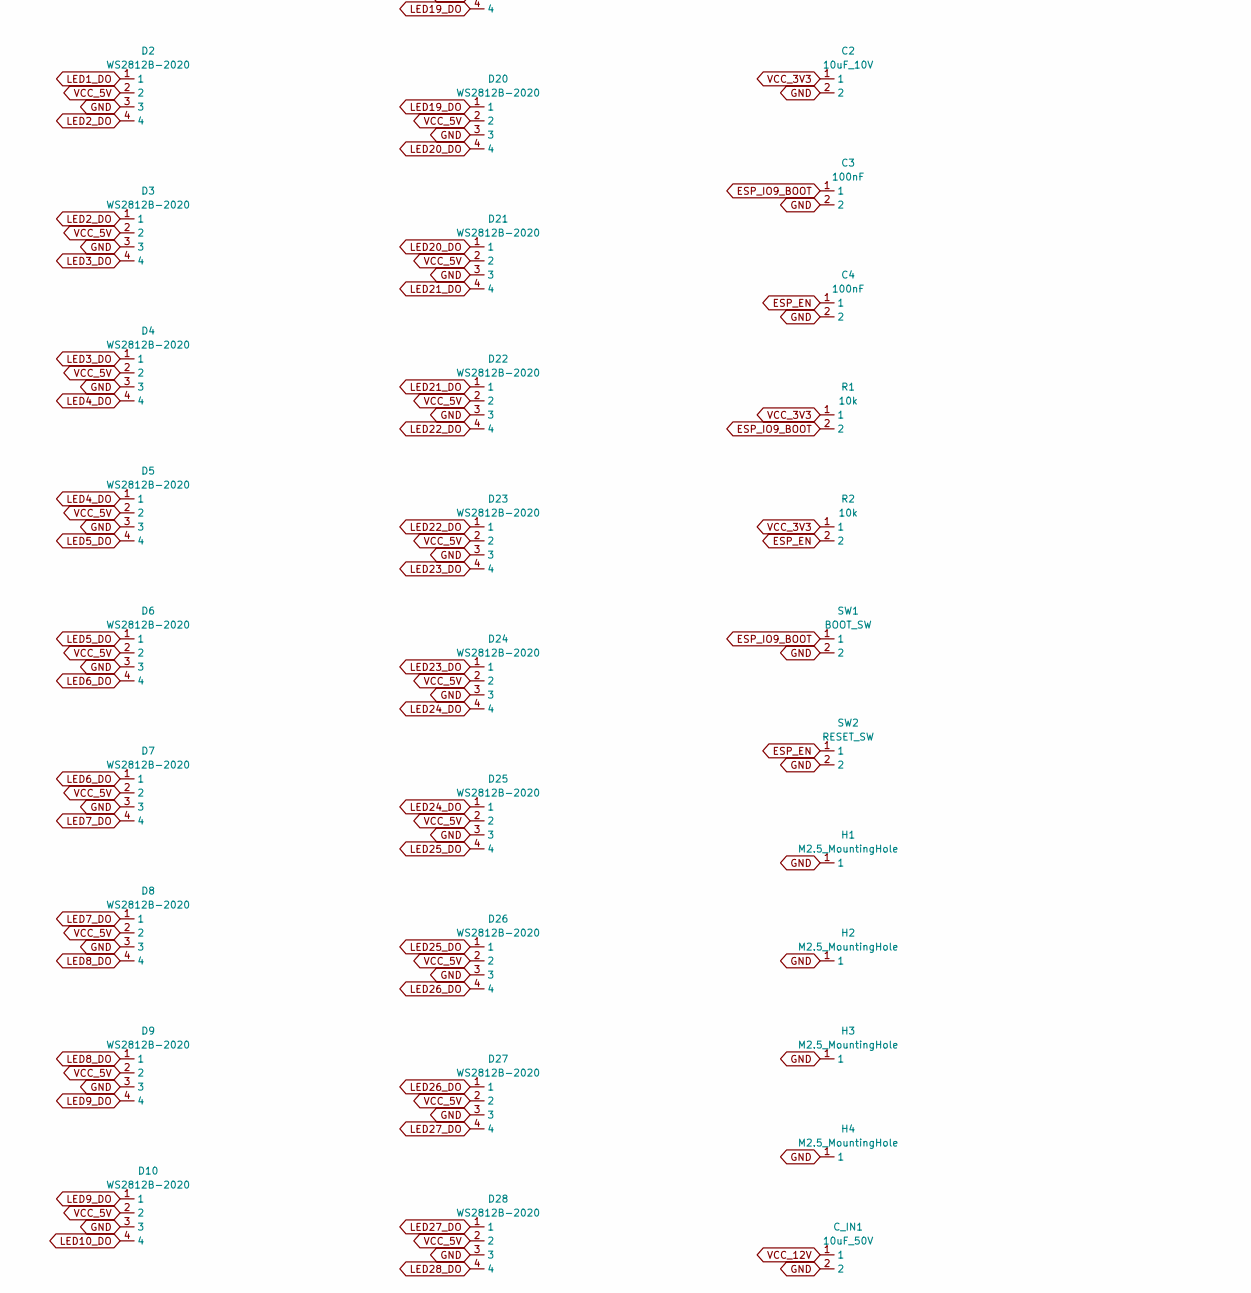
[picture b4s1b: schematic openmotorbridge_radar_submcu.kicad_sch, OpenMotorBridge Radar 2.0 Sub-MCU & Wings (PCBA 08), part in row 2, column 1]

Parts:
C1: 10uF_16V; C_0805_2012Metric
C2: 10uF_10V; C_0805_2012Metric
C3, C4: 100nF; C_0603_1608Metric
C_BOOT: 100nF_BOOT; C_0603_1608Metric
C_IN1: 10uF_50V; C_0805_2012Metric
C_OUT1: 22uF_10V; C_0805_2012Metric
D1, D2, D3, D4, D5, D6, D7, D8, D9, D10, D11, D12, D13, D14, D15, D16, D17, D18, D19, D20, D21, D22, D23, D24, D25, D26, D27, D28, D29, D30, D31, D32, D33, D34, D35, D36: WS2812B-2020; LED_WS2812B-2020_PLCC4_2.0x2.0mm
H1, H2, H3, H4: M2.5_MountingHole; MountingHole_2.7mm_M2.5_Pad
J1: JST_GH_4P_BUS_VERT; JST_GH_BM04B-GHS-TBT_1x04-1MP_P1.25mm_Vertical
J2: JST_SH_4P_MR20_VERT; JST_SH_BM04B-SRSS-TB_1x04-1MP_P1.00mm_Vertical
L1: 4.7uH_Power_Choke; L_Sunlord_MWSA1206S-4R7
R1, R2: 10k; R_0603_1608Metric
R_FB1: 100k_FB1; R_0603_1608Metric
R_FB2: 13.7k_FB2; R_0603_1608Metric
SW1: BOOT_SW; SW_Push_SPST_NO_Alps_SKRK
SW2: RESET_SW; SW_Push_SPST_NO_Alps_SKRK
U1: ESP32-C5-WROOM-1U; ESP32-C3-WROOM-02U
U2: TPS7A0533; SOT-23-5
U3: TPS54302_5V_BUCK; SOT-23-6

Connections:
BUCK_BOOT: C_BOOT.1, U3.1
BUCK_FB: R_FB1.2, R_FB2.1, U3.4
BUCK_SW: C_BOOT.2, L1.1, U3.6
BUS_DM: J1.4, U1.16
BUS_DP: J1.3, U1.17
ESP_EN: C4.1, R2.2, SW2.1, U1.7
ESP_IO9_BOOT: C3.1, R1.2, SW1.1, U1.13
GND: C1.2, C2.2, C3.2, C4.2, C_IN1.2, C_OUT1.2, D1.3, D2.3, D3.3, D4.3, D5.3, D6.3, D7.3, D8.3, D9.3, D10.3, D11.3, D12.3, D13.3, D14.3, D15.3, D16.3, D17.3, D18.3, D19.3, D20.3, D21.3, D22.3, D23.3, D24.3, D25.3, D26.3, D27.3, D28.3, D29.3, D30.3, D31.3, D32.3, D33.3, D34.3, D35.3, D36.3, H1.1, H2.1, H3.1, H4.1, J1.2, J1.MP, J2.2, J2.MP, R_FB2.2, SW1.2, SW2.2, U1.1, U1.9, U1.18, U1.19, U2.2, U3.5
LED1_DO: D1.4, D2.1
LED2_DO: D2.4, D3.1
LED3_DO: D3.4, D4.1
LED4_DO: D4.4, D5.1
LED5_DO: D5.4, D6.1
LED6_DO: D6.4, D7.1
LED7_DO: D7.4, D8.1
LED8_DO: D8.4, D9.1
LED9_DO: D9.4, D10.1
LED10_DO: D10.4, D11.1
LED11_DO: D11.4, D12.1
LED12_DO: D12.4, D13.1
LED13_DO: D13.4, D14.1
LED14_DO: D14.4, D15.1
LED15_DO: D15.4, D16.1
LED16_DO: D16.4, D17.1
LED17_DO: D17.4, D18.1
LED18_DO: D18.4, D19.1
LED19_DO: D19.4, D20.1
LED20_DO: D20.4, D21.1
LED21_DO: D21.4, D22.1
LED22_DO: D22.4, D23.1
LED23_DO: D23.4, D24.1
LED24_DO: D24.4, D25.1
LED25_DO: D25.4, D26.1
LED26_DO: D26.4, D27.1
LED27_DO: D27.4, D28.1
LED28_DO: D28.4, D29.1
LED29_DO: D29.4, D30.1
LED30_DO: D30.4, D31.1
LED31_DO: D31.4, D32.1
LED32_DO: D32.4, D33.1
LED33_DO: D33.4, D34.1
LED34_DO: D34.4, D35.1
LED35_DO: D35.4, D36.1
MR20_RX: J2.4, U1.5
MR20_TX: J2.3, U1.4
VCC_3V3: C2.1, R1.1, R2.1, U1.2, U2.5
VCC_5V: C1.1, C_OUT1.1, D1.2, D2.2, D3.2, D4.2, D5.2, D6.2, D7.2, D8.2, D9.2, D10.2, D11.2, D12.2, D13.2, D14.2, D15.2, D16.2, D17.2, D18.2, D19.2, D20.2, D21.2, D22.2, D23.2, D24.2, D25.2, D26.2, D27.2, D28.2, D29.2, D30.2, D31.2, D32.2, D33.2, D34.2, D35.2, D36.2, J2.1, L1.2, R_FB1.1, U2.1, U2.3
VCC_12V: C_IN1.1, J1.1, U3.2, U3.3
WS2812_DATA: D1.1, U1.8

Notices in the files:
README.md:
Hardware License: CERN-OHL-S v2
Software License: GPL v3
Documentation: CC BY-SA 4.0
